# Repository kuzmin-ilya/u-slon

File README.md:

# u-SLON electrical circuit

u-SLON is small laboratory electrostimulator.  
This project is a part of [x-SLON project](https://github.com/comcon1/x-SLON).  
Please address the maternal project for detailed description.

Device is rather small and is assembled simply. We use the standard firm enclosure and face draft for it is attached. 
Please consult [assembly.txt](case/assembly.txt).

**Scheme of the device output**

Programmator connection is inside the enclosure. Output plugs are only USB and 2 Jacks (6.3 mm).
Pulse output has contacts galvanically separated from the rest circuit. 
Trigger output has the contact with trigger pulses having the fixed positive amplitude and the ground contact.

# Authors

Ilya Kuzmin <kuzmin.ilya@gmail.com>  
Peter Mamonov <pmamonov@gmail.com>  
Alexey Nesterenko <comcon1@protonmail.com>  

# Licensing

"u-SLON electrical circuit" project (I. Kuzmin, P. Mamonov, A. Nesterenko)
is released under license CC BY-SA 3.0.

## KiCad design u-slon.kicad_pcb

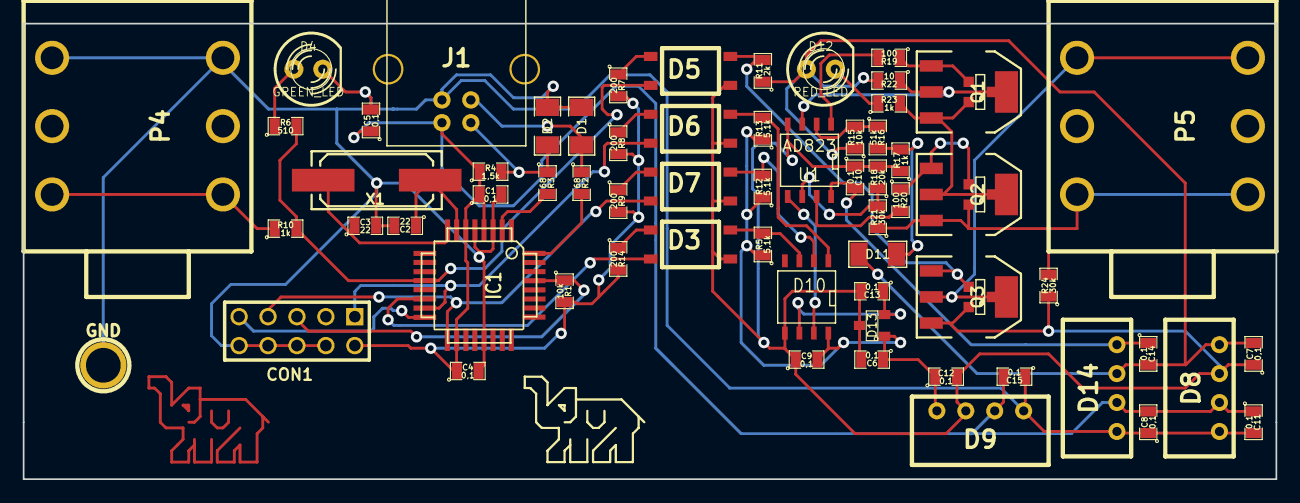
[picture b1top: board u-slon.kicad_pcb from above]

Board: 2 copper layers, 110.0 x 40.0 mm, 67 parts (0 on the bottom side), 42 nets.

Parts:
C1, C4, C5, C6, C7, C8, C9, C10, C11, C12, C13, C14, C15: 0,1; SM0805
C2, C3: 22; SM0805
CON1: AVR-ISP-10; PIN_ARRAY_5x2
D1, D2, D11: 3,3V; SM1206
D3, D5, D6, D7: TLP181GB; TLP181
D4: GREEN_LED; LED-5MM
D8: P6AU-0512ELF; P6AU
D9, D14: P6AU-0505ELF; P6AU
D10: TLC5615CD; SO8N
D12: RED_LED; LED-5MM
D13: REF3020; SOT23
GND: P***; 1pin
IC1: ATMEGA8A-M; TQFP32
J1: USB_B
P4, P5: ST-020
Q1, Q2, Q3: IRFL4310; SOT223
R1, R15: 10k; SM0805
R2, R3: 68; SM0805
R4: 1,5k; SM0805
R5, R12, R13: 5,1k; SM0805
R6: 510; SM0805
R7, R8, R9, R14: 200; SM0805
R10, R17, R23: 1k; SM0805
R11: 2k; SM0805
R16: 51k; SM0805
R18: 20k; SM0805
R19, R20: 100; SM0805
R21, R24: 30k; SM0805
R22: 10; SM0805
SOT23GDS, SOT23GDS#2, SOT23GDS#3: VAL**; SOT23GDS
U1: AD823; SO8N
X1: 12MHz; Q_49U3HMS

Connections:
+5V: C1.1, C4.1, C5.1, C8.2, C11.1, C15.2, CON1.2, D8.2, D9.2, D14.2, IC1.4, IC1.6, IC1.18, J1.1, R1.2, R4.1, R7.2, R8.2, R9.2, R14.2
+5VA: C6.1, C9.2, C12.1, D9.4, D10.8, D13.1, R5.1, R12.1, R13.1
AGND: C6.2, C7.1, C9.1, C10.1, C12.2, C13.2, D3.4, D5.4, D6.4, D7.4, D8.3, D9.3, D10.5, D13.3, Q3.S, R17.1, R18.2, R24.1, U1.4
GND: C1.2, C2.2, C3.2, C4.2, C5.2, C8.1, C11.2, C15.1, CON1.4, CON1.6, CON1.8, CON1.10, D1.1, D2.1, D4.2, D8.1, D9.1, D14.1, IC1.3, IC1.5, IC1.21, J1.4, P4.1, P4.6
unnamed: CON1.1, D6.3, IC1.15
unnamed: D1.2, J1.3, R2.1
unnamed: R19.2, U1.1
unnamed: R20.2, U1.7
unnamed: CON1.9, IC1.16
unnamed: D2.2, J1.2, R3.1, R4.2
unnamed: IC1.32, R2.2
unnamed: IC1.2, R3.2
unnamed: D12.2, R23.1
unnamed: D6.6, D10.1, R13.2
unnamed: D4.1, R6.1
unnamed: P5.1, P5.6, Q3.D
unnamed: P4.3, P4.4, R10.1
unnamed: D10.7, U1.5
unnamed: D5.6, Q3.G, R11.2
unnamed: D7.6, D10.2, R12.2
unnamed: D7.1, R9.1
unnamed: D5.1, R7.1
unnamed: R18.1, R21.2, U1.6
unnamed: R15.2, R16.1, U1.2
unnamed: D11.1, R16.2, R17.2
unnamed: C13.1, D10.6, D13.2
unnamed: D6.1, R8.1
unnamed: Q1.S, Q2.D, R23.2
unnamed: Q1.D, R22.1, U1.3
unnamed: CON1.7, D7.3, IC1.17
unnamed: Q2.G, R20.1
unnamed: Q1.G, R19.1
unnamed: D3.6, D10.3, R5.2
unnamed: D3.3, IC1.14
unnamed: D3.1, R14.1
unnamed: P5.3, P5.4, Q2.S, R21.1, R24.2
unnamed: D5.3, IC1.12, R6.2, R10.2
unnamed: C10.2, C14.1, D14.4, U1.8
unnamed: C3.1, IC1.8, X1.2
unnamed: C2.1, IC1.7, X1.1
unnamed: CON1.5, IC1.29, R1.1
VCC: C7.2, C14.2, D8.4, D11.2, D12.1, D14.3, R11.1, R15.1, R22.2

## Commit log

2018-10-11 moving to git
2018-10-27 The face and the assemblage.
2018-10-27 Pictures
2018-10-27 License and Readme.
2018-10-27 Face was extracted and removed from this file.
2018-10-27 Description of outputs.
2018-10-28 Change 123 to TRS in fig
